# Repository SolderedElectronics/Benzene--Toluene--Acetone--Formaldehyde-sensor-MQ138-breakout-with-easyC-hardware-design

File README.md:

# Benzene, Toluene, Acetone, Formaldehyde sensor MQ138 breakout qwiic Hardware Design

## About the Product

|  |
| :----------------------------------------------------------: |
| [Buy Benzene, Toluene, Acetone, Formaldehyde sensor MQ138 breakout qwiic](https://www.solde.red/333128) |

The MQ138 sensor is specifically designed to detect various gases, with a primary focus on air quality monitoring. While its main target gas is formaldehyde (HCHO), it is also sensitive to a range of other gases, including volatile organic compounds (VOCs) such as toluene, alcohol, acetone, and hydrogen, as well as other harmful gases commonly found in the environment. It requires a short time to heat up in order to work correctly.

The breakout board provides both digital and analog output through the qwiic system. Sensor readings are obtained through the qwiic.

---

## Repository Contents

This repository contains all design files for Benzene, Toluene, Acetone, Formaldehyde sensor MQ138 breakout qwiic, organized as follows:

- **`CAD` folder**: Contains KiCAD design files, including:
  - Schematics
  - PCB layout
  - Panel PCB layout
  - Source 3D files in Fusion360, if any
  - All files are sorted by version with a detailed change log.
- **`OUTPUTS` folder**: Includes all production-ready files, such as:
  - Bill of Materials (BOM) and interactive BOM (iBOM)
  - PDF versions of schematics
  - 3D `.step` file of the board
  - 3D-printable models
  - Gerber files for PCB manufacturing
  - Image of the pinout of the board
  - Product image
  - Compliance, legal and generic sales documents

Refer to the `Change Log` in the CAD folder for details about updates between versions.

---

## Learn More About the Product

Beyond the repository, explore the following resources:

### Soldered Verify

The **Soldered Verify** system ensures every board you purchase from Soldered is fully functional. It also provides access to exclusive test data for your product. To get started, find the unique Soldered Verify ID on your product's packaging and enter the ID on the [Soldered Verify page](https://soldered.com/verify/) to access test results and additional product details.

### Soldered Community

Soldered Community is your go-to place for technical support. Our engineers track and answer all questions posted there, and it’s a great space for the maker community. Get answers to your questions and solutions for your challenges at [Soldered Community](https://soldered.com/community).

### solde.red

solde.red is an ultimate URL shortener and information hub. Access it by typing solde.red/ followed by your product SKU, e.g., [solde.red/333000](https://solde.red/333000), to find getting-started guides, datasheets, open-source hardware and software files, certifications, images, pinouts, and more. Read more about the shortener [here](https://solde.red/info/).

---

## Contributing

Contributions are welcome! Here’s how you can get involved:

- Submit pull requests to enhance the design or fix issues.
- Report bugs or problems by opening an issue.

We encourage community collaboration to make this product even better.

---

## About Soldered

[Soldered for Makers](https://soldered.com) specializes in designing and manufacturing electronic products tailored for enthusiasts, ranging from hobbyists to professionals. Our portfolio includes electronic boards, sensors, and actuators that are widely utilized in fields such as microelectronics, mechatronics, robotics, programming, and IoT. Every product we offer is designed in-house and built upon open-source hardware and software platforms. Proudly certified and manufactured within the European Union, our catalog likely includes the product you need for your project.

We complement these products with comprehensive tutorials and manuals, product descriptions, schematics, programming codes, and project examples. Our round-the-clock [customer and technical support](https://soldered.com/community) is available for all our products, irrespective of the sales channel. Soldered’s success and services reflect our maker community’s unwavering [trust](https://www.trustpilot.com/review/soldered.com), for which we are deeply grateful. Join our community and create using Soldered products.

---

## License

All Soldered open-source hardware (OSH) is under The TAPR Open Hardware License. Read more in the LICENSE file located in this repository.

**Disclaimer:**

No warranty - all designs in this repository are distributed in the hope that they will be useful, but without any warranty. They are provided "AS IS", therefore without warranty of any kind, either expressed or implied. The entire quality and performance of what you do with the contents of this repository are your responsibility. In no event Soldered Electronics will be liable for your damages, or losses, including any general, special, incidental, or consequential damage arising out of the use or inability to use the contents of this repository. 

---

## Have fun!

Thank you for your support from your fellow makers at Soldered Electronics.

Happy Making!

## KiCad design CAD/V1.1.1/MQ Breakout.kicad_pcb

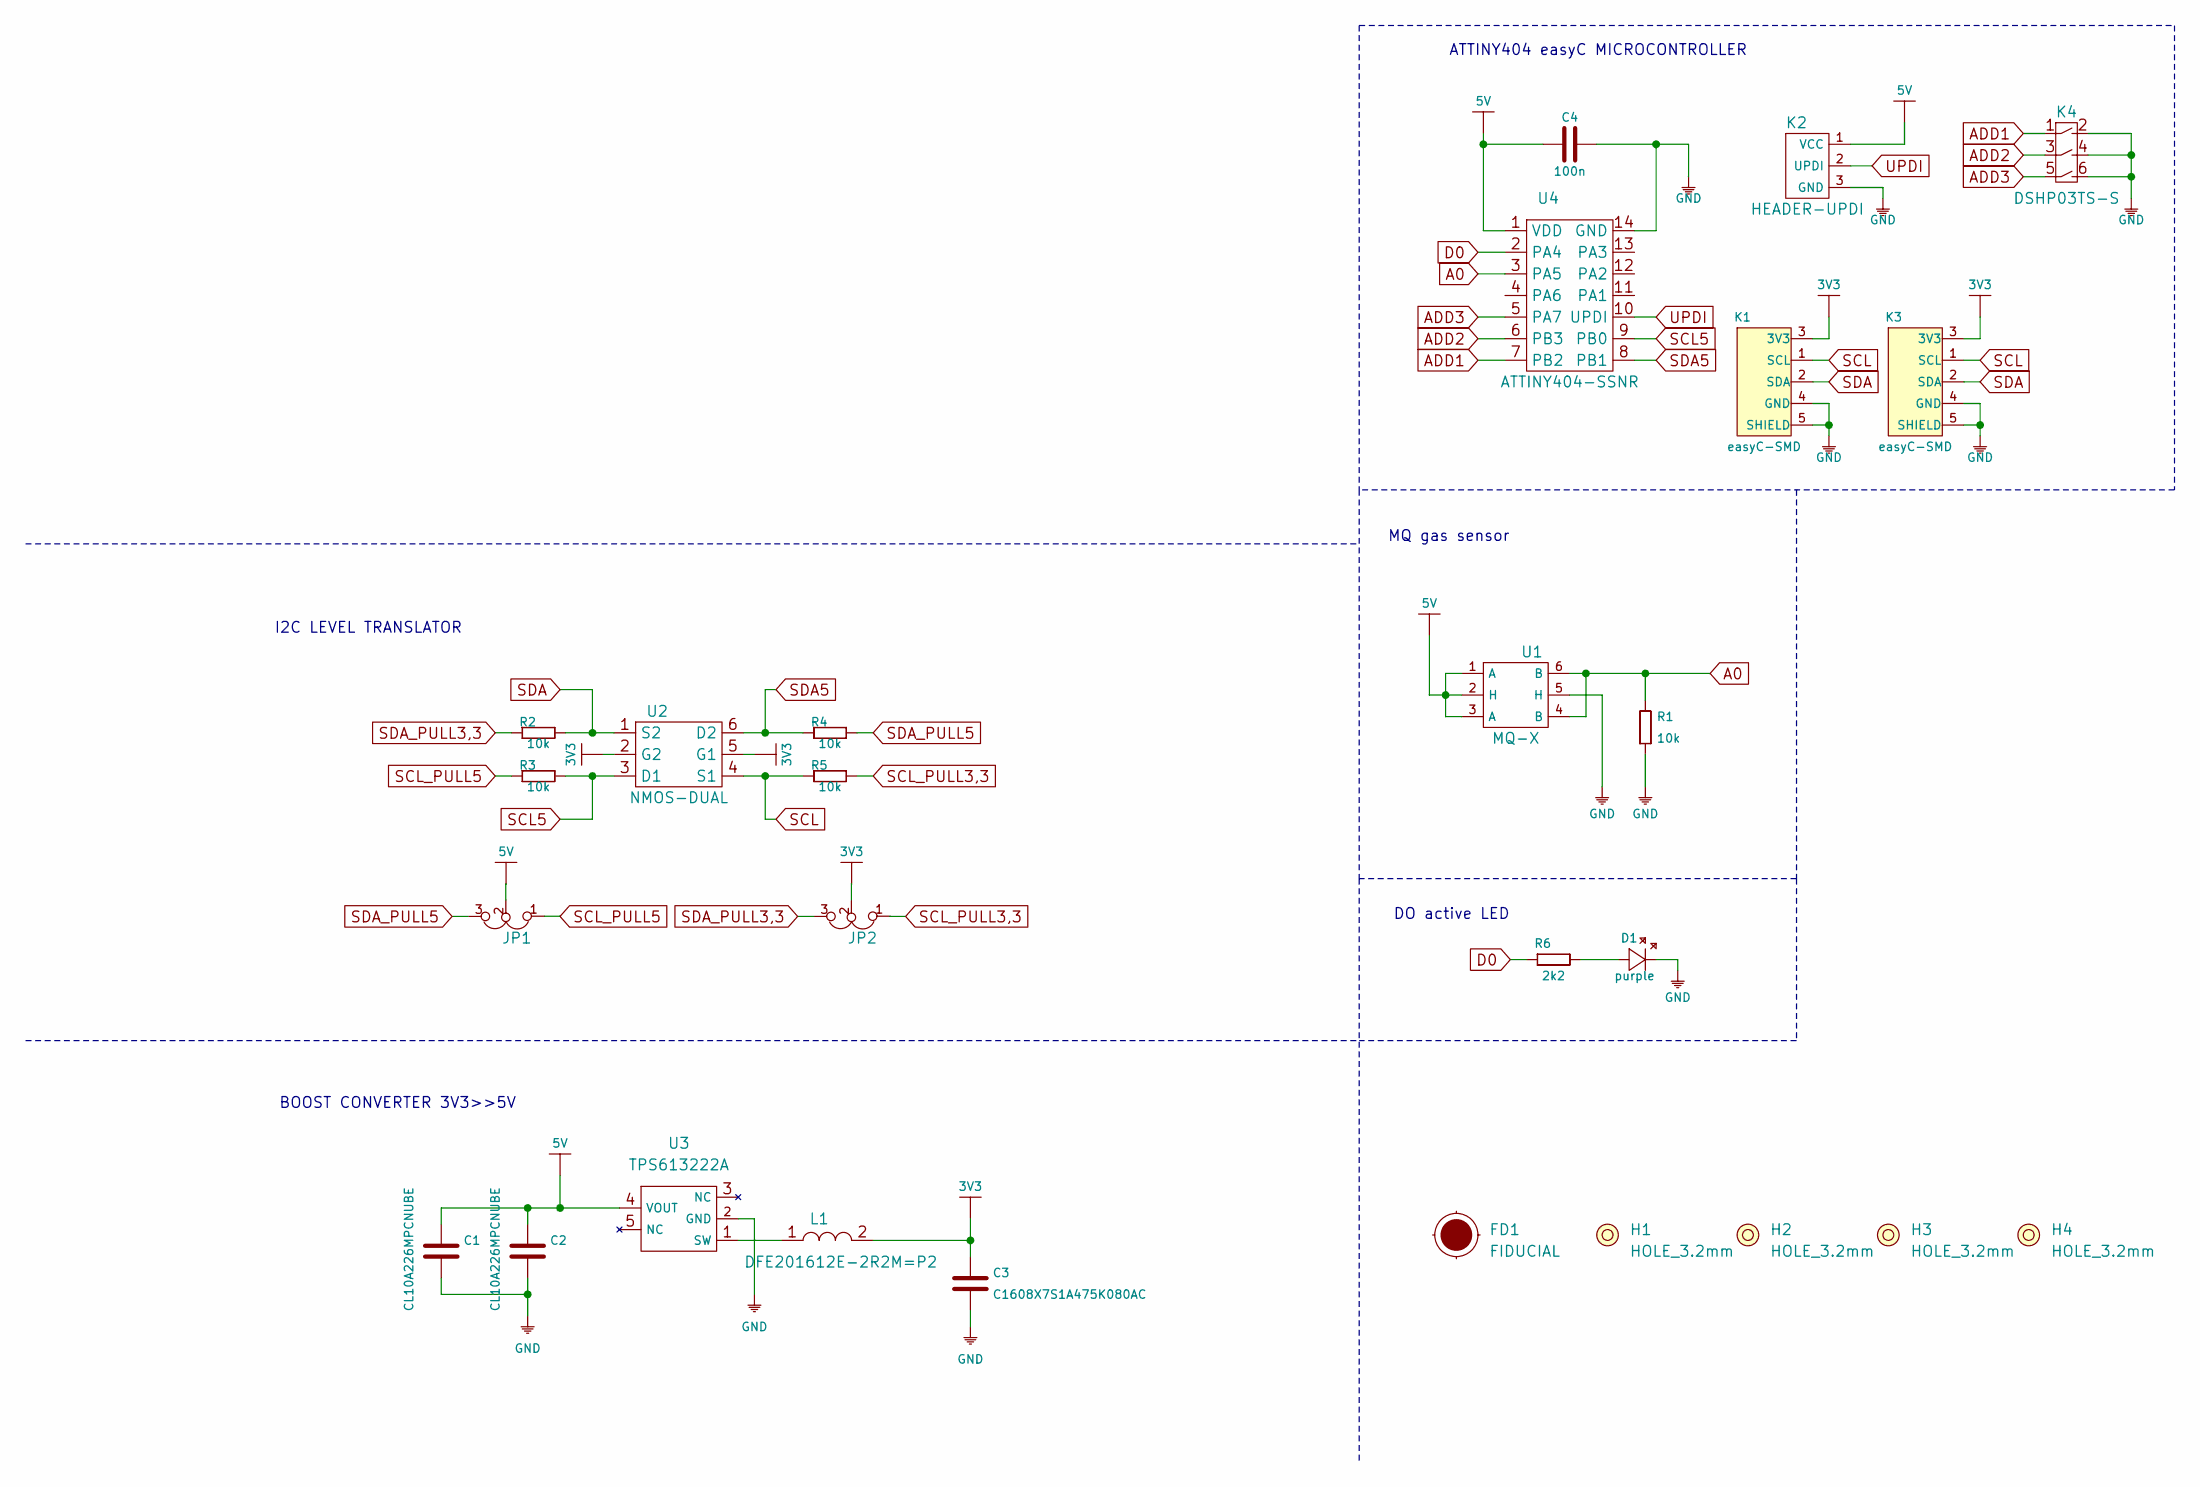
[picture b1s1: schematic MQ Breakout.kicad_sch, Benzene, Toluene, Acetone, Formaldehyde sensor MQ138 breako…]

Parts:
C1, C2: CL10A226MPCNUBE; 0805C
C3: C1608X7S1A475K080AC; 0805C
C4: 100n; 0603C
D1: purple; 0402LED
FD1: FIDUCIAL; FIDUCIAL_23
H1, H2, H3, H4: HOLE_3.2mm
JP1, JP2: SMD_JUMPER_3_PAD_TRACE
K1, K3: easyC-SMD; easyC-connector
K2: HEADER-UPDI
K4: DSHP03TS-S
L1: DFE201612E-2R2M=P2; 0806L
R1, R2, R3, R4, R5: 10k; 0603R
R6: 2k2; 0402R
U1: MQ-X; MQ
U2: NMOS-DUAL; SOT-363
U3: TPS613222A; tps613222a
U4: ATTINY404-SSNR; SOIC-14

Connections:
3V3: C3.2, JP2.2, K1.3 (3V3), K3.3 (3V3), L1.2, U2.2 (G2), U2.5 (G1)
5V: C1.2, C2.2, C4.1, JP1.2, K2.1 (VCC), U1.1 (A), U1.2 (H), U1.3 (A), U3.4 (VOUT), U4.1 (VDD)
A0: R1.2, U1.4 (B), U1.6 (B), U4.3 (PA5)
ADD1: K4.1, U4.7 (PB2)
ADD2: K4.3, U4.6 (PB3)
ADD3: K4.5, U4.5 (PA7)
D0: R6.1, U4.2 (PA4)
GND: C1.1, C2.1, C3.1, C4.2, D1.2 (K), K1.4 (GND), K1.5 (SHIELD), K2.3 (GND), K3.4 (GND), K3.5 (SHIELD), K4.2, K4.4, K4.6, R1.1, U1.5 (H), U3.2 (GND), U4.14 (GND)
unnamed: D1.1 (A), R6.2
unnamed: L1.1, U3.1 (SW)
SCL: K1.1 (SCL), K3.1 (SCL), R5.1, U2.4 (S1)
SCL5: R3.2, U2.3 (D1), U4.9 (PB0)
SCL_PULL3,3: JP2.1, R5.2
SCL_PULL5: JP1.1, R3.1
SDA: K1.2 (SDA), K3.2 (SDA), R2.2, U2.1 (S2)
SDA5: R4.1, U2.6 (D2), U4.8 (PB1)
SDA_PULL3,3: JP2.3, R2.1
SDA_PULL5: JP1.3, R4.2
UPDI: K2.2 (UPDI), U4.10 (UPDI)

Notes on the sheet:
ATTINY404 easyC MICROCONTROLLER
MQ gas sensor
I2C LEVEL TRANSLATOR
DO active LED
BOOST CONVERTER 3V3>>5V

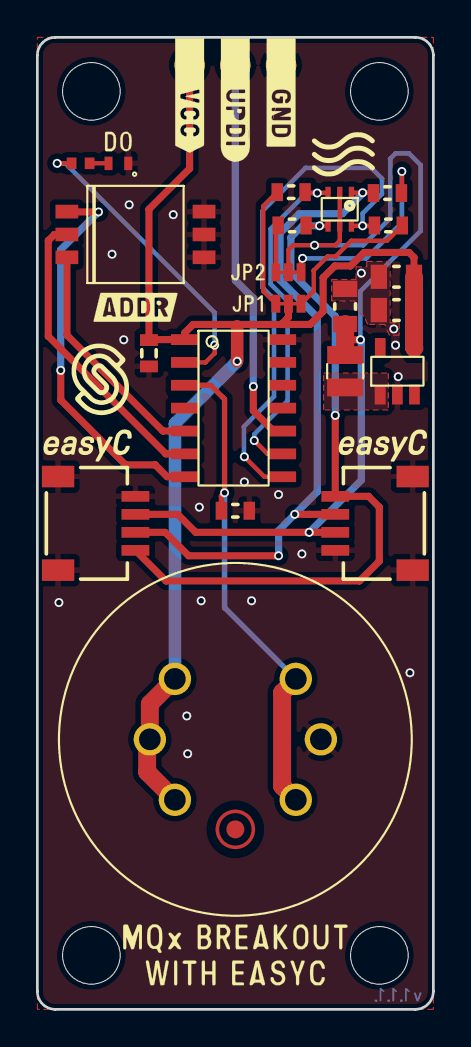
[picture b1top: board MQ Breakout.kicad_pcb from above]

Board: 2 copper layers, 22.0 x 54.0 mm, 27 parts (0 on the bottom side), 19 nets.

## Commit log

2022-08-06 Updating open source files.
